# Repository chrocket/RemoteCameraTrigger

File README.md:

# RemoteCameraTrigger

SF30ReadEchoLCD2wWire  - Program  for - SF30 Lidar, LCD screen and trigger out to separate board with transmitter

CameraTriggerR2PCB  - PCB and software - Main camera trigger board using Adafruit LoRo module
CameraTriggerSensorNodeOnly - PCB and software - Sensor node only

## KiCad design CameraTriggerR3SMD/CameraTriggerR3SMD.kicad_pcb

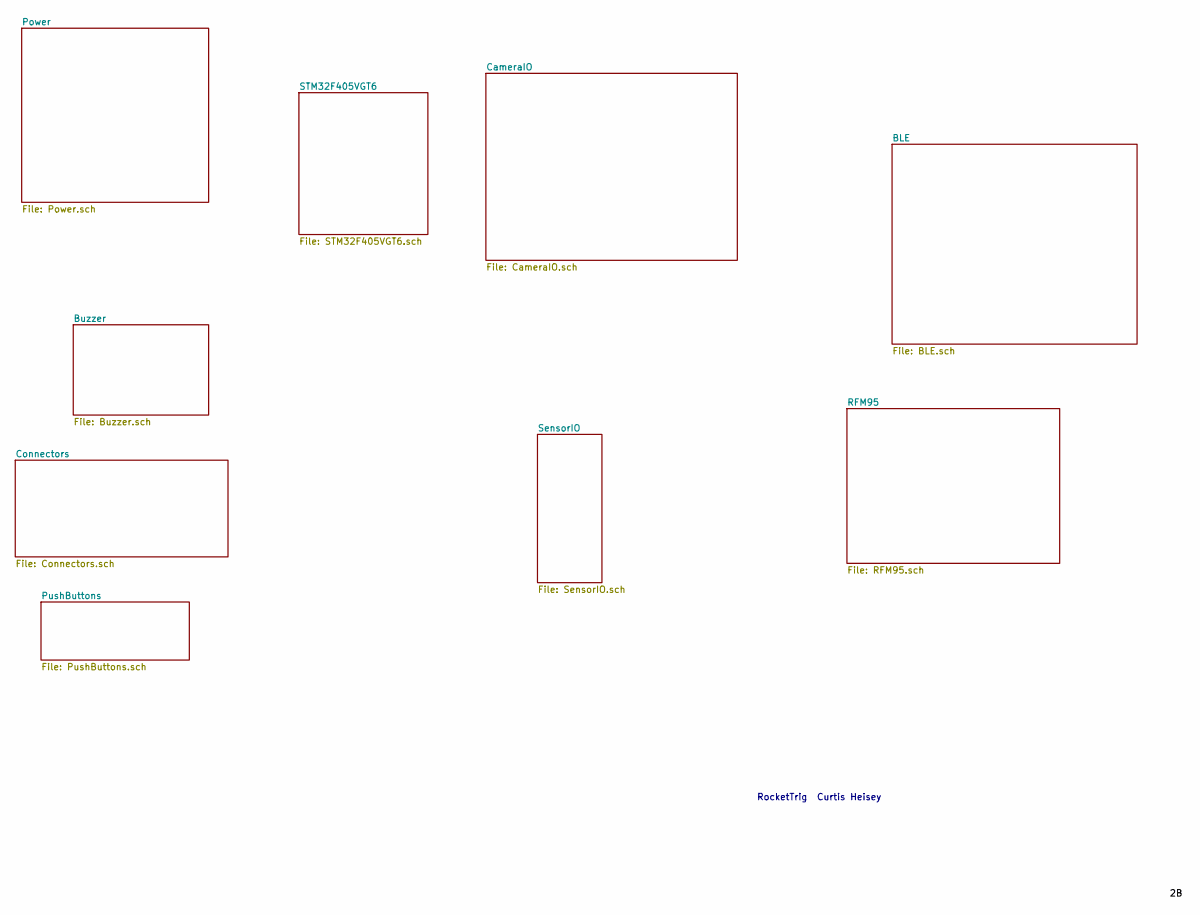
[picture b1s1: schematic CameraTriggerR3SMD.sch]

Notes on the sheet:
RocketTrig Curtis Heisey

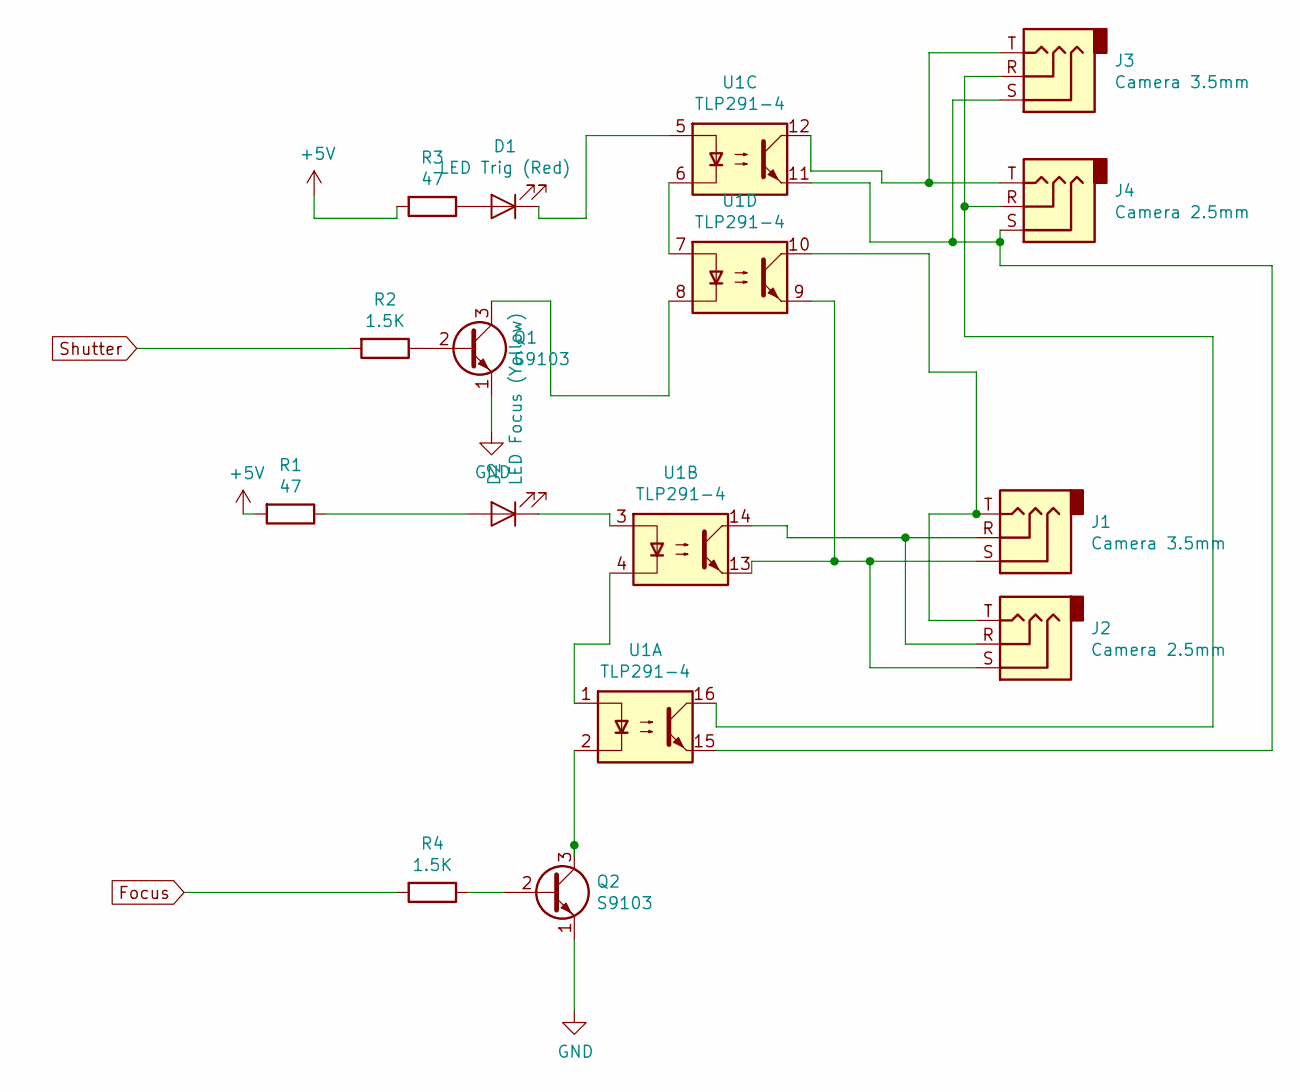
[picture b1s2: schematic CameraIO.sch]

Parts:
D1: LED Trig (Red); LED_0603_1608Metric; LCSC C2286
D2: LED Focus (Yellow); LED_0603_1608Metric; LCSC C72038
J1, J3: Camera 3.5mm; Jack_3.5mm_CUI_SJ1-3533NG_Horizontal_CircularHoles
J2, J4: Camera 2.5mm; CUI_SJ1-2503A
Q1, Q2: S9103; SOT-23; LCSC C6749
R1, R3: 47; R_0402_1005Metric; LCSC C25118
R2, R4: 1.5K; R_0603_1608Metric; LCSC C22843
U1: TLP291-4; SOIC-16_4.55x10.3mm_P1.27mm; LCSC C60900

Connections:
+5V: R1.2, R3.2; also elsewhere on the board
Focus: R4.2; also elsewhere on the board
GND: Q1.1 (E), Q2.1 (E); also elsewhere on the board
unnamed: D1.1 (K), U1.5
unnamed: D1.2 (A), R3.1
unnamed: D2.1 (K), U1.3
unnamed: D2.2 (A), R1.1
unnamed: J1.R, J2.R, U1.14
unnamed: J1.S, J2.S, U1.9, U1.13
unnamed: J1.T, J2.T, U1.10
unnamed: J3.R, J4.R, U1.16
unnamed: J3.S, J4.S, U1.11, U1.15
unnamed: J3.T, J4.T, U1.12
unnamed: Q1.2 (B), R2.1
unnamed: Q1.3 (C), U1.8
unnamed: Q2.2 (B), R4.1
unnamed: Q2.3 (C), U1.2
unnamed: U1.1, U1.4
unnamed: U1.6, U1.7
Shutter: R2.2; also elsewhere on the board

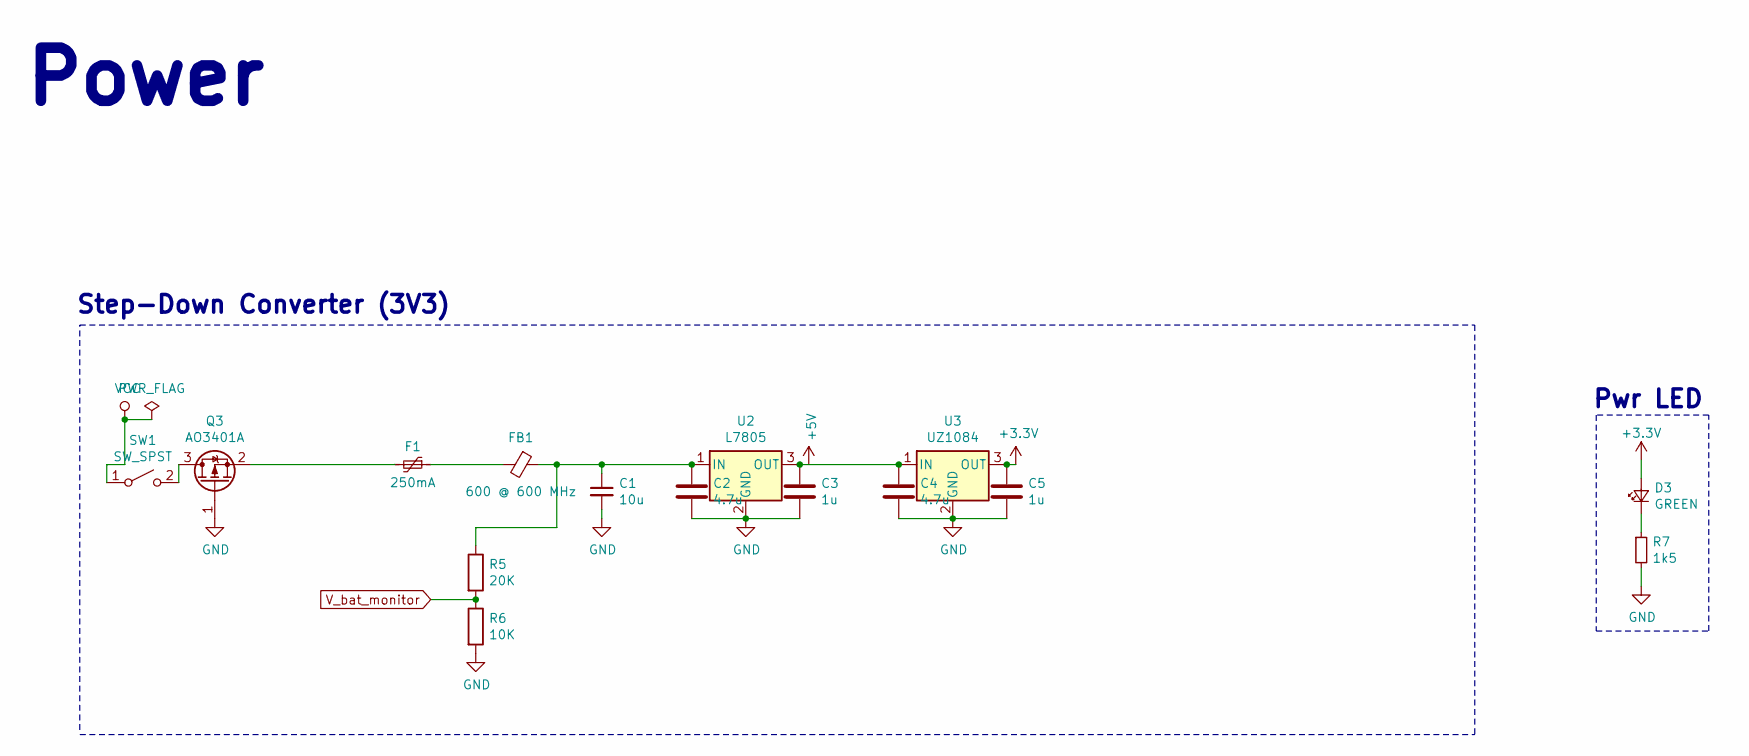
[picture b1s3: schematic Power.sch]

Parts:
C1: 10u; C_1206_3216Metric; LCSC C13585
C2, C4: 4.7u; C_0603_1608Metric; LCSC C19666
C3, C5: 1u; C_0402_1005Metric; LCSC C52923
D3: GREEN; LED_0603_1608Metric; LCSC C72043
F1: 250mA; Fuse_1206_3216Metric; LCSC C70068
FB1: 600 @ 600 MHz; L_0805_2012Metric; LCSC C1017
Q3: AO3401A; SOT-23; LCSC C15127
R5: 20K; R_0603_1608Metric; LCSC C4184
R6: 10K; R_0402_1005Metric; LCSC C25744
R7: 1k5; R_0603_1608Metric; LCSC C22843
SW1: SW_SPST; SW_DIP_SPSTx01_Slide_9.78x4.72mm_W7.62mm_P2.54mm
U2: L7805; TO-252-2; LCSC C310413
U3: UZ1084; TO-252-2; LCSC C84897

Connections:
+3V3: C5.1, D3.2 (A), U3.3 (OUT); also elsewhere on the board
+5V: C3.1, C4.1, U2.3 (OUT), U3.1 (IN); also elsewhere on the board
GND: C1.2, C2.2, C3.2, C4.2, C5.2, Q3.1 (G), R6.2, R7.2, U2.2 (GND), U3.2 (GND); also elsewhere on the board
unnamed: C1.1, C2.1, FB1.1, R5.1, U2.1 (IN)
unnamed: D3.1 (K), R7.1
unnamed: F1.1, FB1.2
unnamed: F1.2, Q3.2 (S)
unnamed: Q3.3 (D), SW1.2 (B)
VCC: SW1.1 (A); also elsewhere on the board
V_bat_monitor: R5.2, R6.1; also elsewhere on the board

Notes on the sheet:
Power
Step-Down Converter (3V3)
Pwr LED

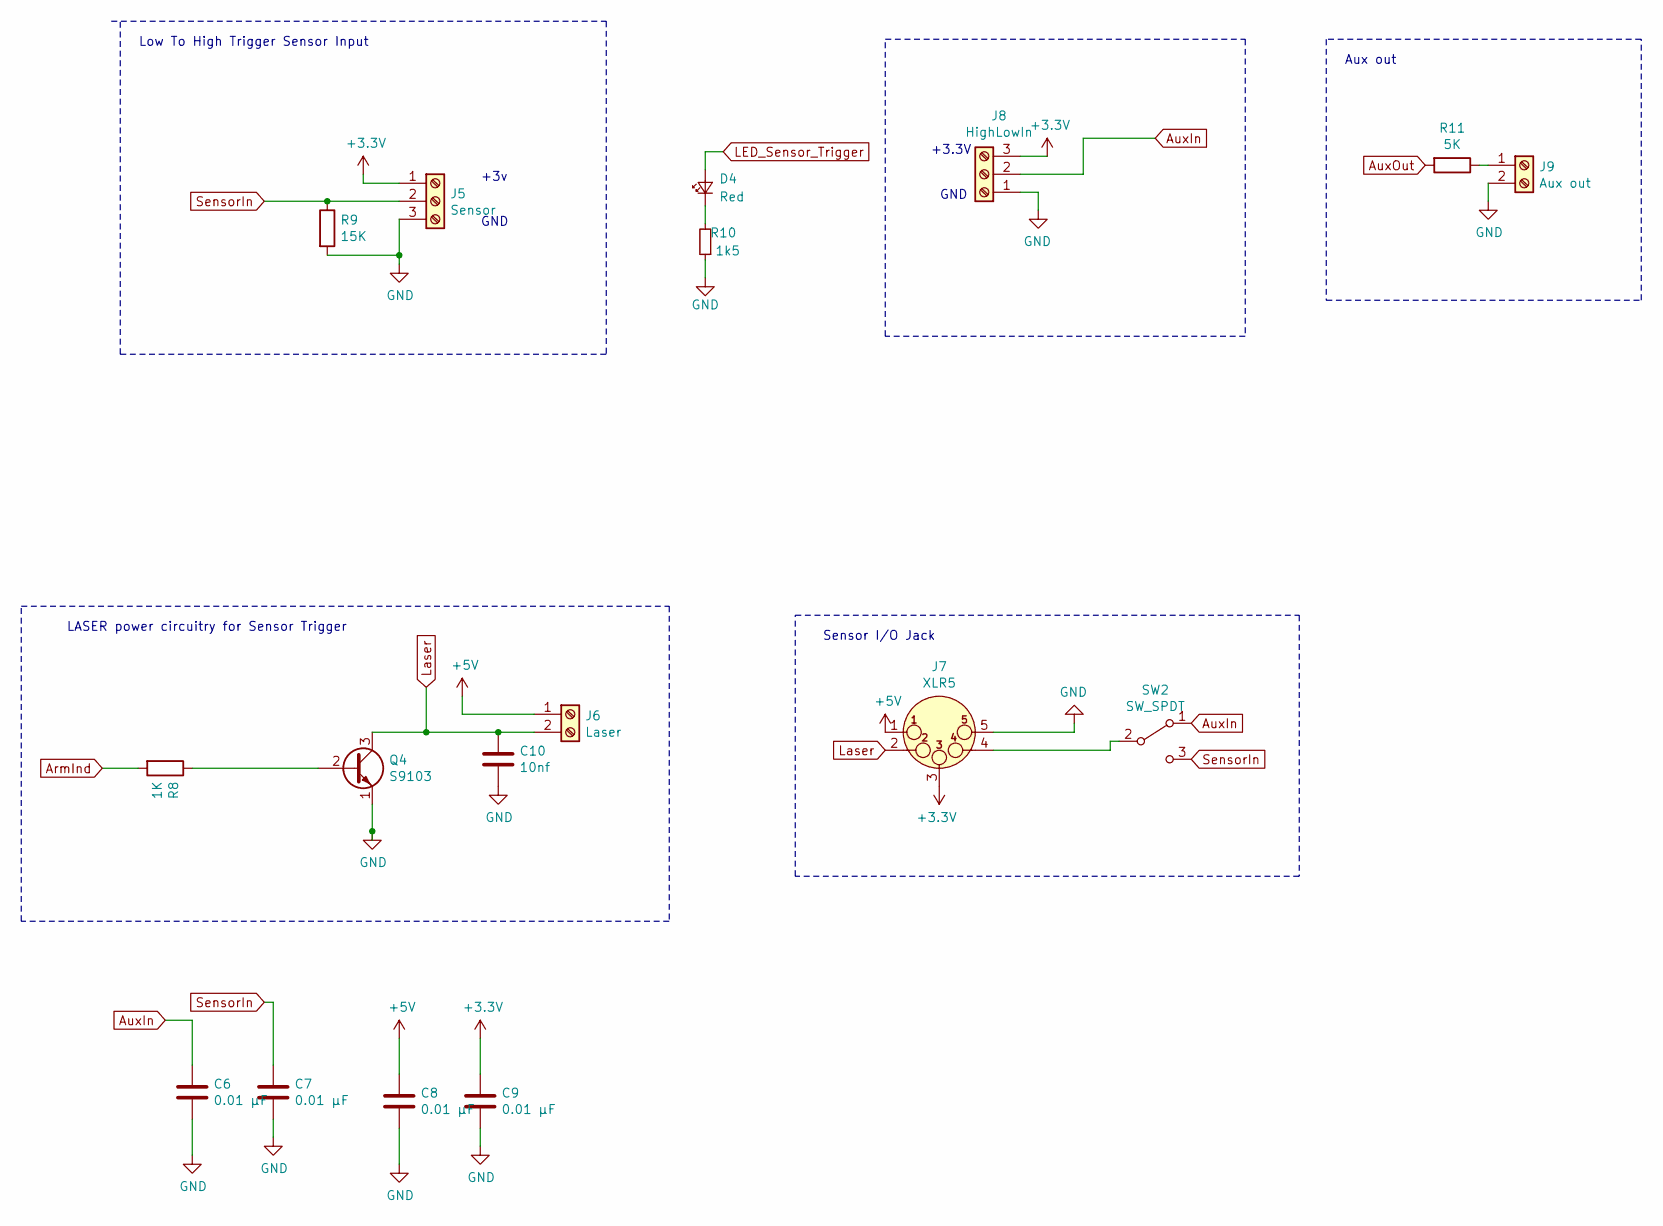
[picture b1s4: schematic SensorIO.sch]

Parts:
C6, C7, C8, C9: 0.01 μF; C_0402_1005Metric; LCSC C1525
C10: 10nf; C_0402_1005Metric; LCSC C15195
D4: Red; LED_0603_1608Metric; LCSC C2286
J5: Sensor; TerminalBlock_TE_282834-3_1x03_P2.54mm_Horizontal
J6: Laser; TerminalBlock_TE_282834-2_1x02_P2.54mm_Horizontal
J7: XLR5; Jack_XLR_Neutrik_NC5MBH_Horizontal
J8: HighLowIn; TerminalBlock_TE_282834-3_1x03_P2.54mm_Horizontal
J9: Aux out; TerminalBlock_TE_282834-2_1x02_P2.54mm_Horizontal
Q4: S9103; SOT-23; LCSC C6749
R8: 1K; R_0603_1608Metric; LCSC C21190
R9: 15K; R_0603_1608Metric; LCSC C22809
R10: 1k5; R_0603_1608Metric; LCSC C22843
R11: 5K; R_0402_1005Metric; LCSC C25744
SW2: SW_SPDT; SW_Slide_1P2T_CK_OS102011MS2Q

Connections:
+3V3: C9.1, J5.1, J7.3, J8.3; also elsewhere on the board
+5V: C8.1, J6.1, J7.1; also elsewhere on the board
ArmInd: R8.2; also elsewhere on the board
AuxIn: C6.1, J8.2, SW2.1 (A); also elsewhere on the board
AuxOut: R11.2; also elsewhere on the board
GND: C6.2, C7.2, C8.2, C9.2, C10.2, J5.3, J7.5, J8.1, J9.2, Q4.1 (E), R9.2, R10.1; also elsewhere on the board
LED_Sensor_Trigger: D4.2 (A); also elsewhere on the board
Laser: C10.1, J6.2, J7.2, Q4.3 (C)
unnamed: D4.1 (K), R10.2
unnamed: J7.4 (P3), SW2.2 (B)
unnamed: J9.1, R11.1
unnamed: Q4.2 (B), R8.1
SensorIn: C7.1, J5.2, R9.1, SW2.3 (C); also elsewhere on the board

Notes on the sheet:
+3v
GND
+3.3V
Low To High Trigger Sensor Input
Aux out
Sensor I/O Jack
LASER power circuitry for Sensor Trigger

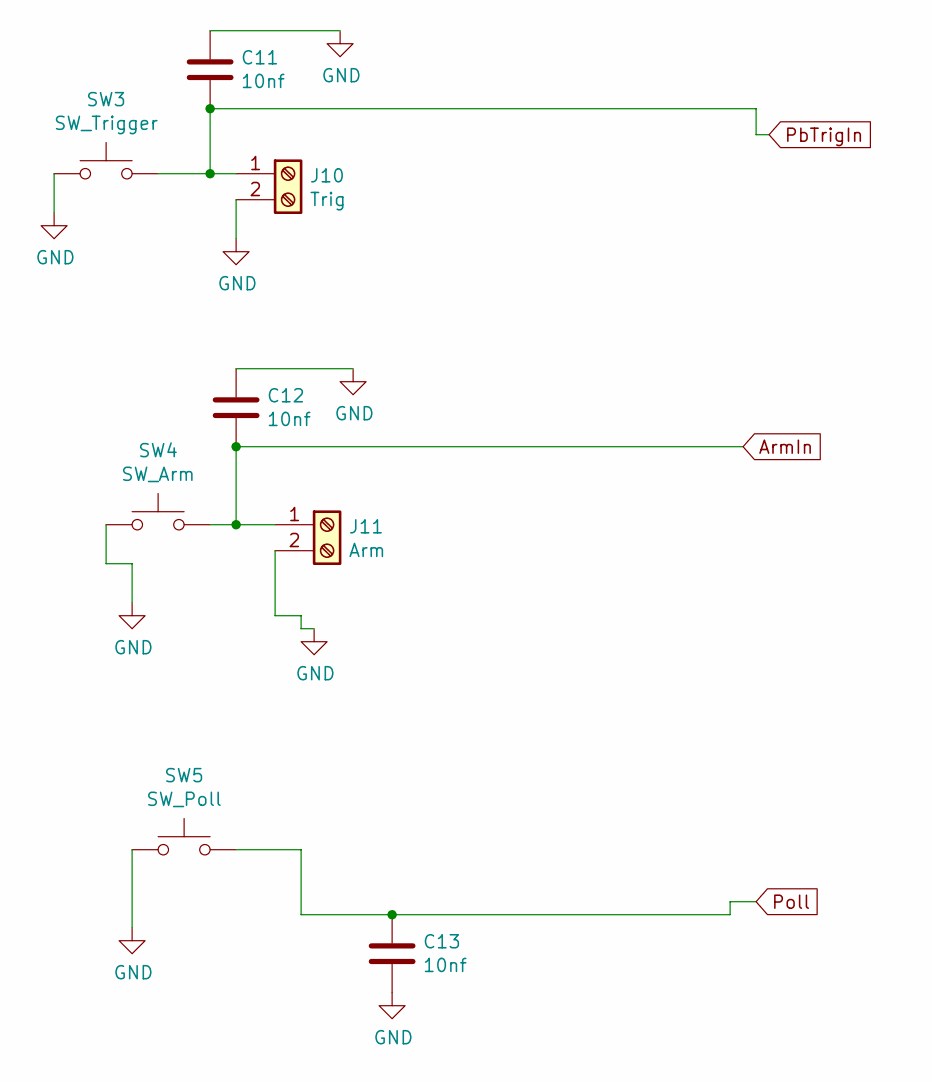
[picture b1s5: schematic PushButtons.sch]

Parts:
C11, C12, C13: 10nf; C_0402_1005Metric; LCSC C15195
J10: Trig; TerminalBlock_TE_282834-2_1x02_P2.54mm_Horizontal
J11: Arm; TerminalBlock_TE_282834-2_1x02_P2.54mm_Horizontal
SW3: SW_Trigger; KSA_Tactile_SPST; LCSC C127509
SW4: SW_Arm; KSA_Tactile_SPST; LCSC C127509
SW5: SW_Poll; KSA_Tactile_SPST; LCSC C127509

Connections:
ArmIn: C12.2, J11.1, SW4.2; also elsewhere on the board
GND: C11.1, C12.1, C13.2, J10.2, J11.2, SW3.1, SW4.1, SW5.1; also elsewhere on the board
PbTrigIn: C11.2, J10.1, SW3.2; also elsewhere on the board
Poll: C13.1, SW5.2; also elsewhere on the board

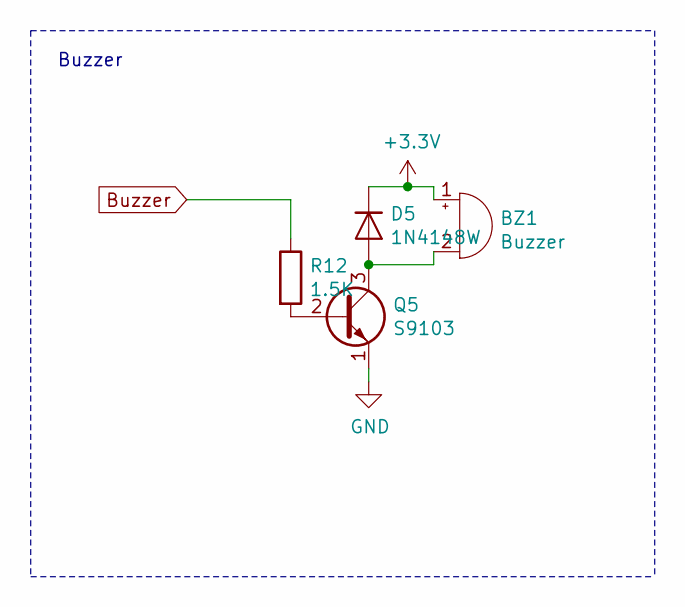
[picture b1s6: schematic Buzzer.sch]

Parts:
BZ1: Buzzer; Buzzer_TDK_PS1240P02BT_D12.2mm_H6.5mm
D5: 1N4148W; D_SOD-323F; LCSC C2128
Q5: S9103; SOT-23; LCSC C6749
R12: 1.5K; R_0603_1608Metric; LCSC C22843

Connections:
+3V3: BZ1.1 (-), D5.1 (K); also elsewhere on the board
Buzzer: R12.1; also elsewhere on the board
GND: Q5.1 (E); also elsewhere on the board
unnamed: BZ1.2 (+), D5.2 (A), Q5.3 (C)
unnamed: Q5.2 (B), R12.2

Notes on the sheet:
Buzzer

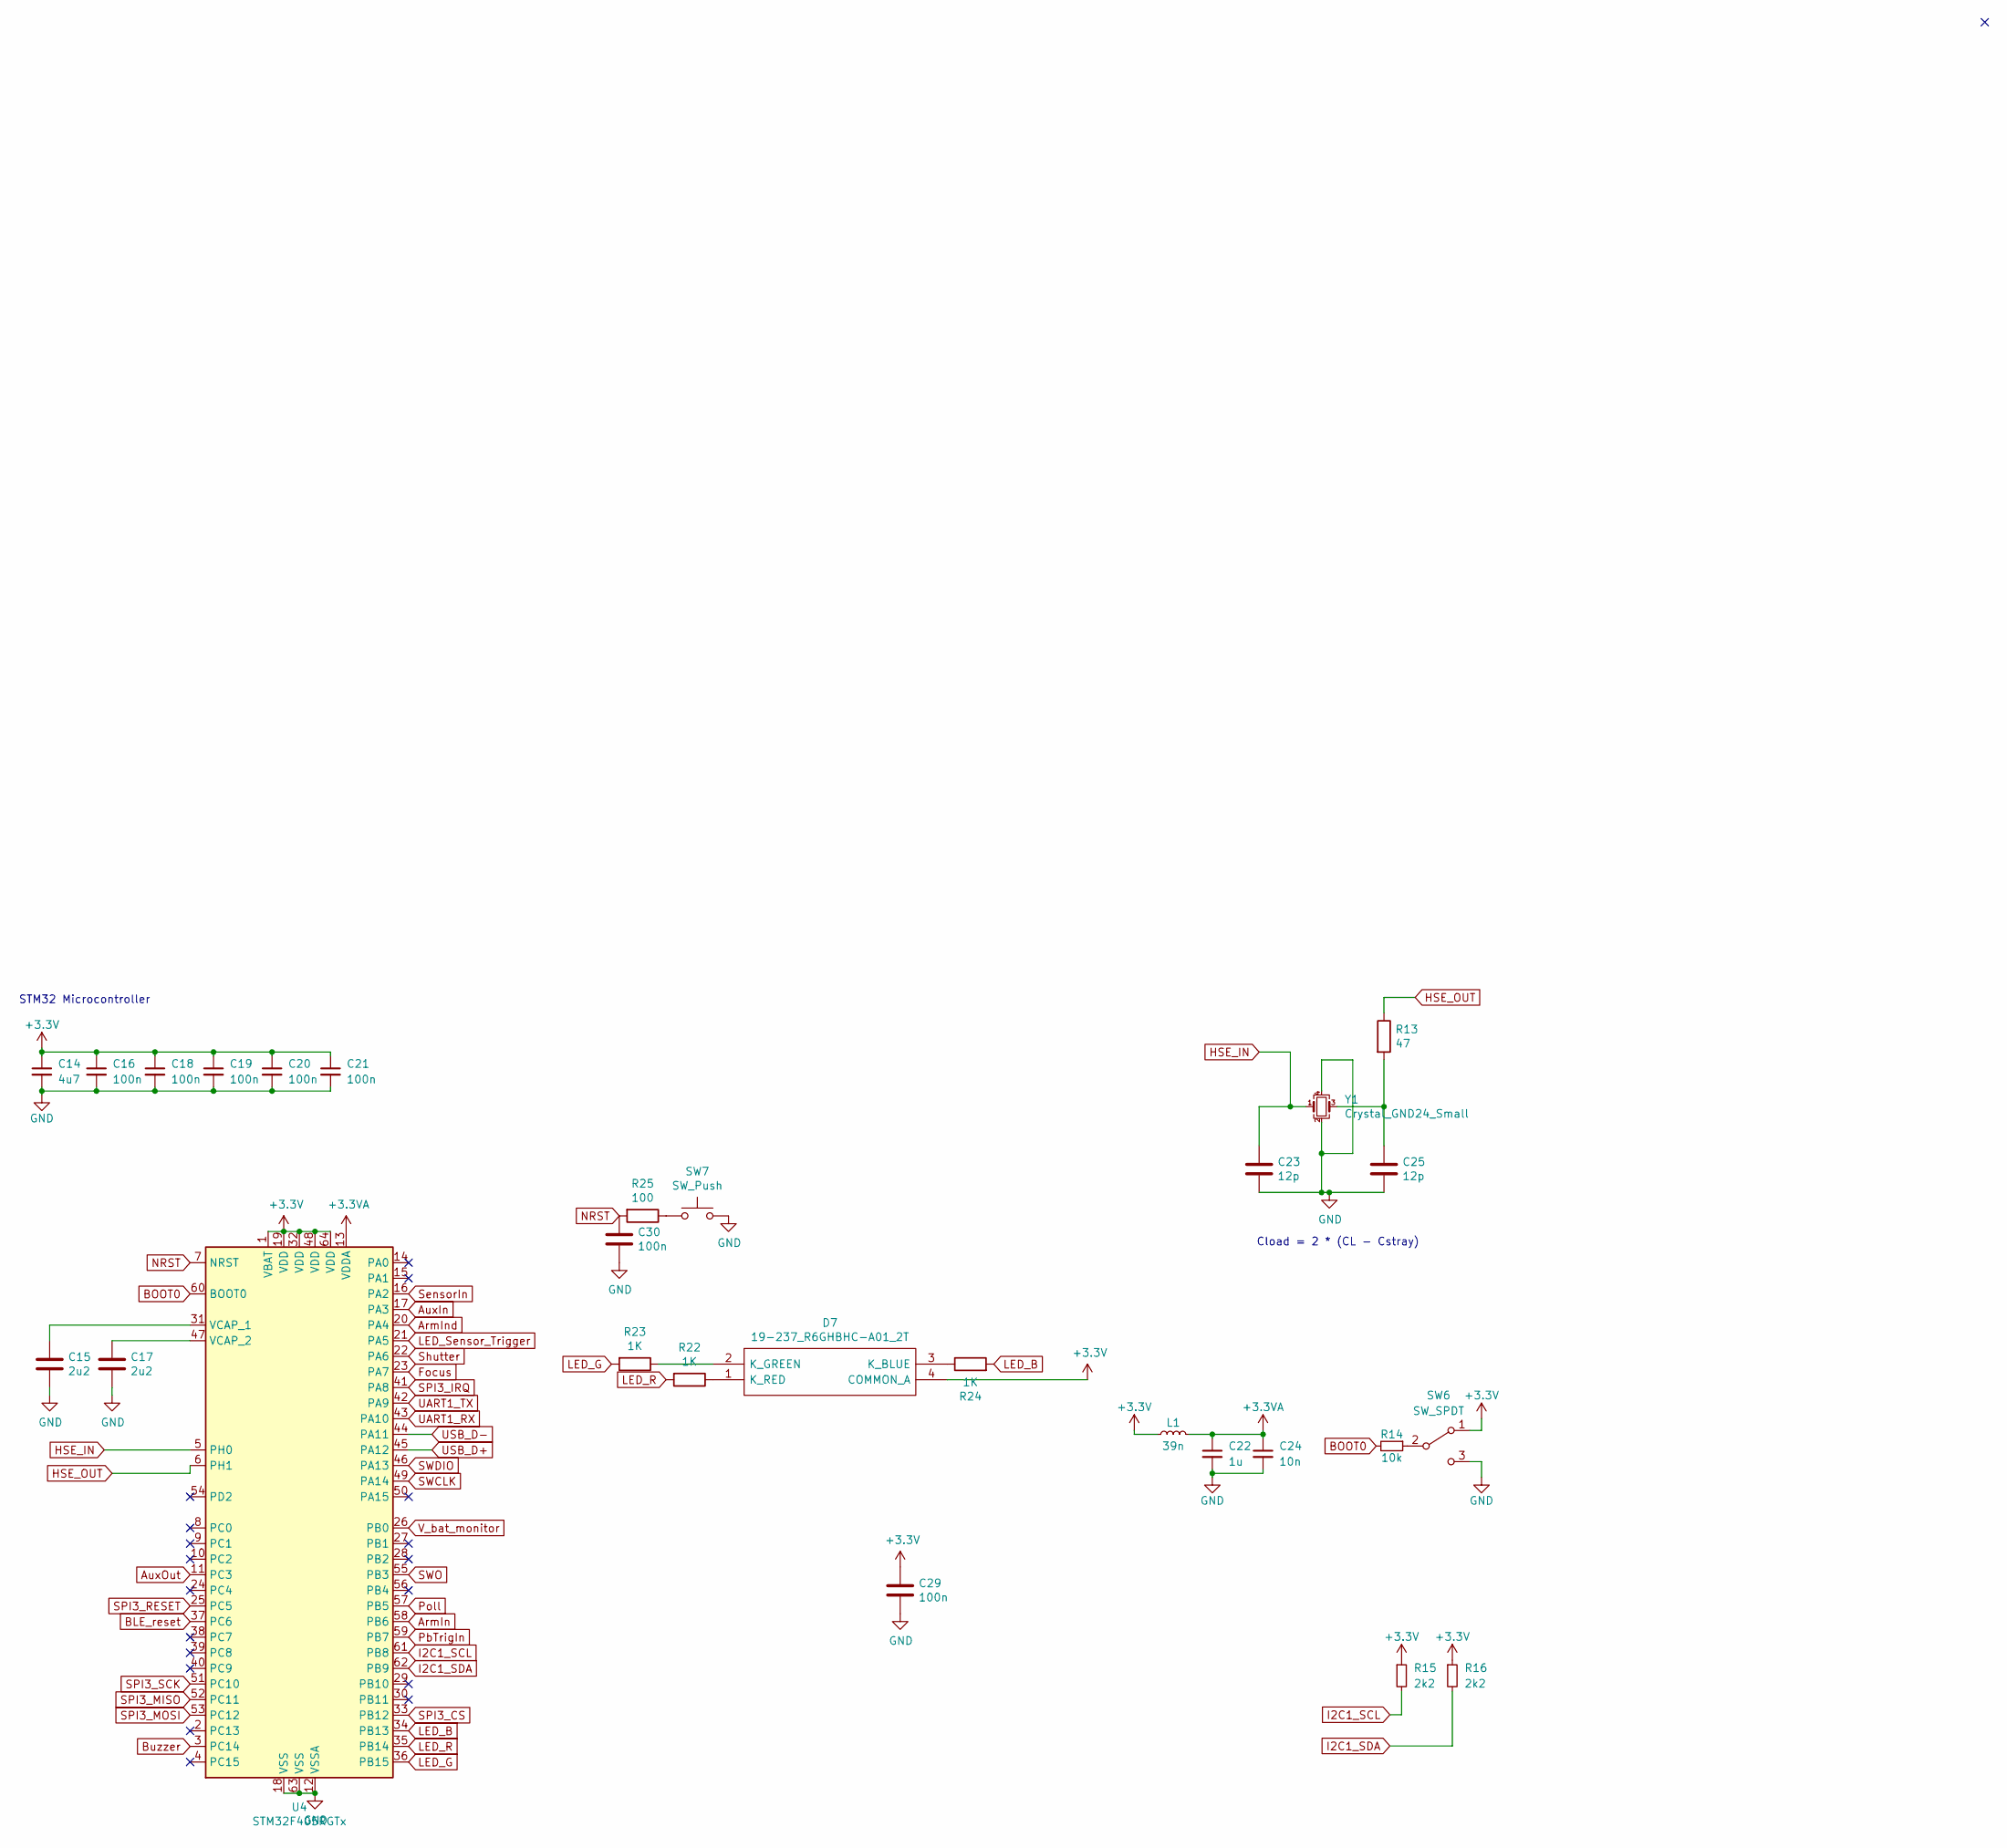
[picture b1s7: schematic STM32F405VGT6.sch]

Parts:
C14: 4u7; C_0603_1608Metric; LCSC C19666
C15, C17: 2u2; C_0603_1608Metric; LCSC C23630
C16, C18, C19, C20, C21: 100n; C_0402_1005Metric; LCSC C1525
C22: 1u; C_0402_1005Metric; LCSC C52923
C23, C25: 12p; C_0402_1005Metric; LCSC C1547
C24: 10n; C_0402_1005Metric; LCSC C15195
C29, C30: 100n; C_0402_1005Metric
D7: 19-237_R6GHBHC-A01_2T; 19237R6GHBHCA012T; Manufacturer_Part_Number 19-237/R6GHBHC-A01/2T; LCSC C60105
L1: 39n; L_0402_1005Metric; LCSC C26443
R13: 47; R_0402_1005Metric; LCSC C25118
R14: 10k; R_0402_1005Metric; LCSC C25744
R15, R16: 2k2; R_0402_1005Metric; LCSC C25879
R22, R23, R24: 1K; R_0402_1005Metric; LCSC C11702
R25: 100; R_0603_1608Metric; LCSC C22775
SW6: SW_SPDT; SW_SPDT_PCM12
SW7: SW_Push; SW_SPST_CK_KXT3
U4: STM32F405RGTx; LQFP-64_10x10mm_P0.5mm; LCSC C15742
Y1: Crystal_GND24_Small; Crystal_SMD_3225-4Pin_3.2x2.5mm; LCSC C13738

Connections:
+3.3VA: C22.1, C24.1, L1.2, U4.13 (VDDA)
+3V3: C14.1, C16.1, C18.1, C19.1, C20.1, C21.1, C29.1, D7.4 (COMMON_A), L1.1, R15.1, R16.1, SW6.1 (A), U4.1 (VBAT), U4.19 (VDD), U4.32 (VDD), U4.48 (VDD), U4.64 (VDD); also elsewhere on the board
ArmIn: U4.58 (PB6); also elsewhere on the board
ArmInd: U4.20 (PA4); also elsewhere on the board
AuxIn: U4.17 (PA3); also elsewhere on the board
AuxOut: U4.11 (PC3); also elsewhere on the board
BLE_reset: U4.37 (PC6); also elsewhere on the board
BOOT0: R14.2, U4.60 (BOOT0)
Buzzer: U4.3 (PC14); also elsewhere on the board
Focus: U4.23 (PA7); also elsewhere on the board
GND: C14.2, C15.2, C16.2, C17.2, C18.2, C19.2, C20.2, C21.2, C22.2, C23.2, C24.2, C25.2, C29.2, C30.2, SW6.3 (C), SW7.2, U4.12 (VSSA), U4.18 (VSS), U4.63 (VSS), Y1.2, Y1.4; also elsewhere on the board
HSE_IN: C23.1, U4.5 (PH0), Y1.1
HSE_OUT: R13.1, U4.6 (PH1)
I2C1_SCL: R15.2, U4.61 (PB8); also elsewhere on the board
I2C1_SDA: R16.2, U4.62 (PB9); also elsewhere on the board
LED_B: R24.2, U4.34 (PB13)
LED_G: R23.2, U4.36 (PB15)
LED_R: R22.2, U4.35 (PB14)
LED_Sensor_Trigger: U4.21 (PA5); also elsewhere on the board
NRST: C30.1, R25.2, U4.7 (NRST); also elsewhere on the board
unnamed: C15.1, U4.31 (VCAP_1)
unnamed: C17.1, U4.47 (VCAP_2)
unnamed: C25.1, R13.2, Y1.3
unnamed: D7.1 (K_RED), R22.1
unnamed: D7.2 (K_GREEN), R23.1
unnamed: D7.3 (K_BLUE), R24.1
unnamed: R14.1, SW6.2 (B)
unnamed: R25.1, SW7.1
PbTrigIn: U4.59 (PB7); also elsewhere on the board
Poll: U4.57 (PB5); also elsewhere on the board
SPI3_CS: U4.33 (PB12); also elsewhere on the board
SPI3_IRQ: U4.41 (PA8); also elsewhere on the board
SPI3_MISO: U4.52 (PC11); also elsewhere on the board
SPI3_MOSI: U4.53 (PC12); also elsewhere on the board
SPI3_RESET: U4.25 (PC5); also elsewhere on the board
SPI3_SCK: U4.51 (PC10); also elsewhere on the board
SWCLK: U4.49 (PA14); also elsewhere on the board
SWDIO: U4.46 (PA13); also elsewhere on the board
SWO: U4.55 (PB3); also elsewhere on the board
SensorIn: U4.16 (PA2); also elsewhere on the board
Shutter: U4.22 (PA6); also elsewhere on the board
UART1_RX: U4.43 (PA10); also elsewhere on the board
UART1_TX: U4.42 (PA9); also elsewhere on the board
USB_D+: U4.45 (PA12); also elsewhere on the board
USB_D-: U4.44 (PA11); also elsewhere on the board
V_bat_monitor: U4.26 (PB0); also elsewhere on the board

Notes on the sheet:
Cload = 2 * (CL - Cstray)
STM32 Microcontroller

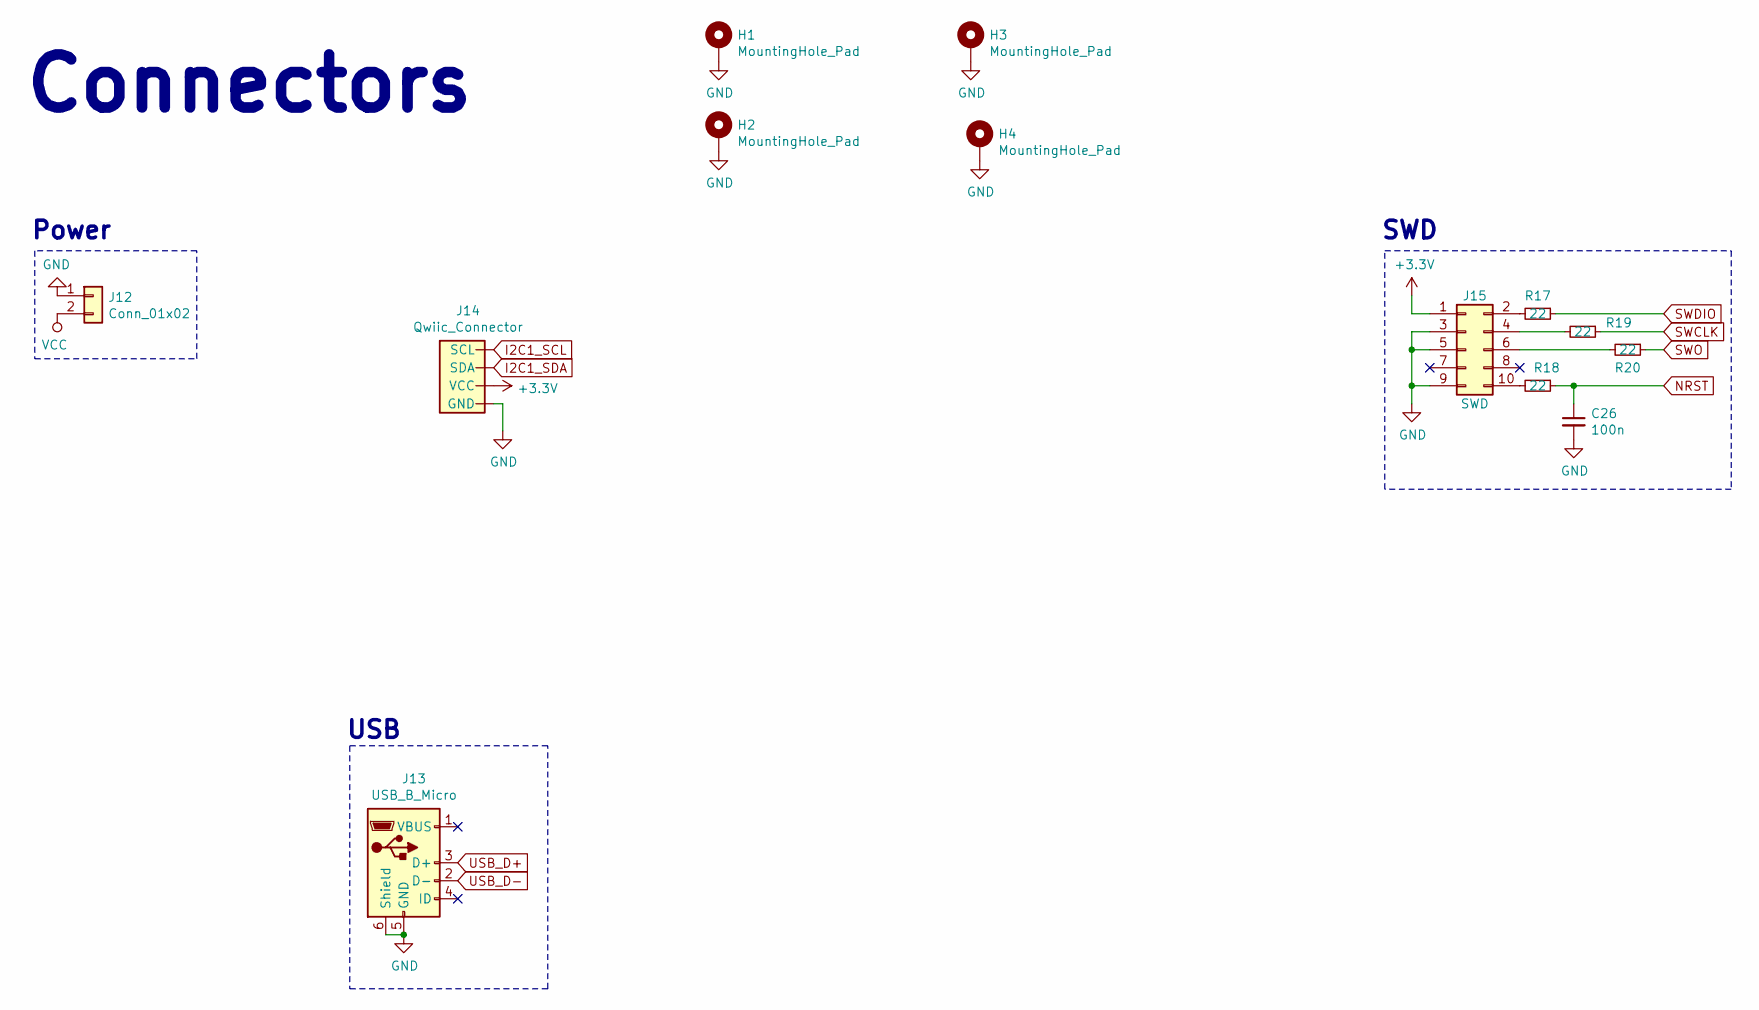
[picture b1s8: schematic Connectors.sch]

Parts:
C26: 100n; C_0402_1005Metric; LCSC C1525
H1, H2, H3, H4: MountingHole_Pad; MountingHole_3.2mm_M3_Pad_Via
J12: Conn_01x02; AMASS_XT30U-F_1x02_P5.0mm_Vertical
J13: USB_B_Micro; USB_Micro-B_Wuerth_629105150521
J14: Qwiic_Connector; 1X04_1MM_RA_STRESSRELIEF
J15: SWD; PinHeader_2x05_P1.27mm_Vertical_SMD
R17, R18, R19, R20: 22; R_0402_1005Metric; LCSC C25092

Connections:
+3V3: J14.2 (VCC), J15.1; also elsewhere on the board
GND: C26.2, H1.1, H2.1, H3.1, H4.1, J12.1, J13.5 (GND), J13.6 (Shield), J14.1 (GND), J15.3, J15.5, J15.9; also elsewhere on the board
I2C1_SCL: J14.4 (SCL); also elsewhere on the board
I2C1_SDA: J14.3 (SDA); also elsewhere on the board
NRST: C26.1, R18.1; also elsewhere on the board
unnamed: J15.2, R17.2
unnamed: J15.4, R19.2
unnamed: J15.6, R20.2
unnamed: J15.10, R18.2
SWCLK: R19.1; also elsewhere on the board
SWDIO: R17.1; also elsewhere on the board
SWO: R20.1; also elsewhere on the board
USB_D+: J13.3 (D+); also elsewhere on the board
USB_D-: J13.2 (D-); also elsewhere on the board
VCC: J12.2; also elsewhere on the board

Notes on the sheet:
Connectors
USB
Power
SWD

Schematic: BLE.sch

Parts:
C27: 100n; C_0402_1005Metric; LCSC C1525
D6: BLUE; LED_0603_1608Metric; LCSC C72041
R21: 1k5; R_0603_1608Metric; LCSC C22843
U5: RN4871; Microchip_RN4871

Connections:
+3V3: C27.1, U5.14 (VBAT); also elsewhere on the board
BLE_reset: U5.10 (RST); also elsewhere on the board
GND: C27.2, R21.1, U5.2 (GND), U5.13 (GND); also elsewhere on the board
LED_TXRX: D6.2 (A), U5.11 (P0_0)
unnamed: D6.1 (K), R21.2
UART1_RX: U5.8 (UART_TX); also elsewhere on the board
UART1_TX: U5.7 (UART_RX); also elsewhere on the board

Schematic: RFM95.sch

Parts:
C28: 10nf; C_0402_1005Metric; Partno C0805C103J4HACTU; LCSC C15195
J16: Conn_Coaxial; SMA_Amphenol_132289_EdgeMount; Partno 132289
U6: RFM95W-915S2; HOPERF_RFM9XW_THT

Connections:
+3V3: C28.1, U6.13 (3.3V); also elsewhere on the board
GND: C28.2, J16.2 (Ext), U6.1 (GND), U6.8 (GND), U6.10 (GND); also elsewhere on the board
unnamed: J16.1 (In), U6.9 (ANT)
SPI3_CS: U6.5 (NSS); also elsewhere on the board
SPI3_IRQ: U6.14 (DIO0); also elsewhere on the board
SPI3_MISO: U6.2 (MISO); also elsewhere on the board
SPI3_MOSI: U6.3 (MOSI); also elsewhere on the board
SPI3_RESET: U6.6 (RESET); also elsewhere on the board
SPI3_SCK: U6.4 (SCK); also elsewhere on the board

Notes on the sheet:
LoRa 'Radio using RFM95 Based on Feather M0 LoRa Adafruit 3178

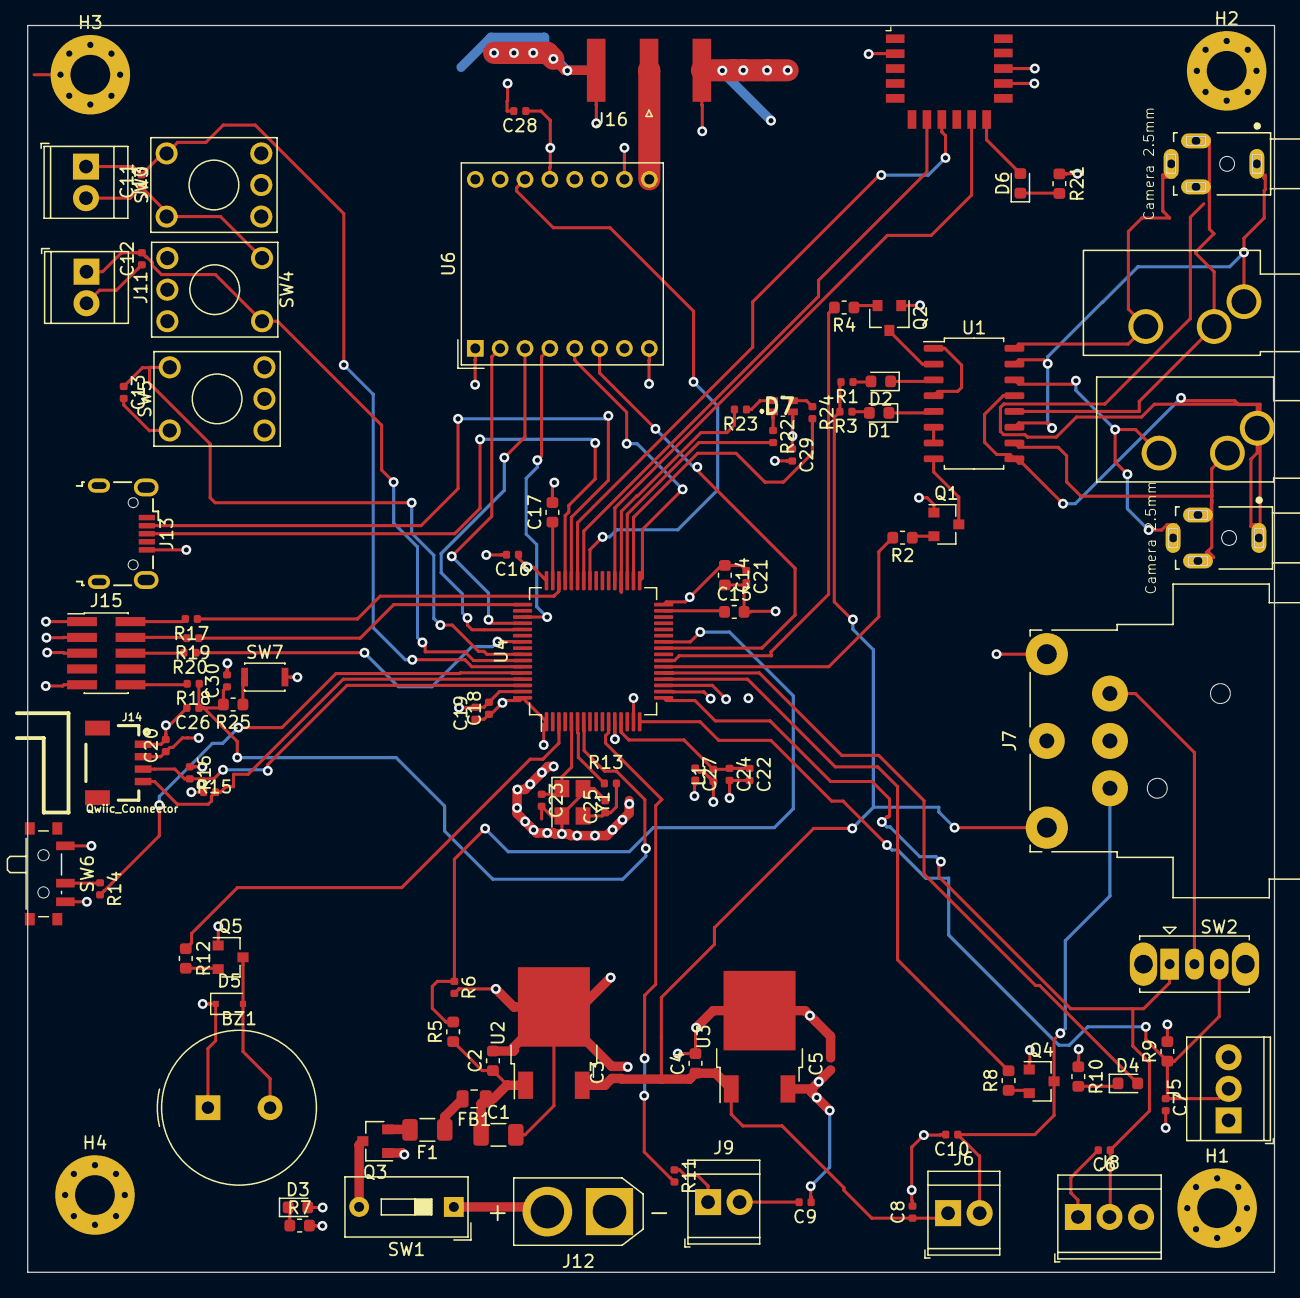
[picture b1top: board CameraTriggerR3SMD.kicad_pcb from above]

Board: 4 copper layers, 100.3 x 100.3 mm, 105 parts (0 on the bottom side), 83 nets.
